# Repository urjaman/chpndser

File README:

CH340g-based debug serial dongle for the pandora ext port
----------------------------------------------------------

Parts list:
- usb mini b connector
- ch340g
- NX3008NBKW,115 SOT-323 n-ch mosfet
- 12Mhz HC-49 SMD crystal
- 2* 22pF 0603 cap
- 2* 0.1u 0603 cap
- 4* 4k7 0603 resistors
- pandora ext port connector

The PCB is shared at oshpark:
https://oshpark.com/shared_projects/jlOmwnKj
remember to pick the 0.8mm service

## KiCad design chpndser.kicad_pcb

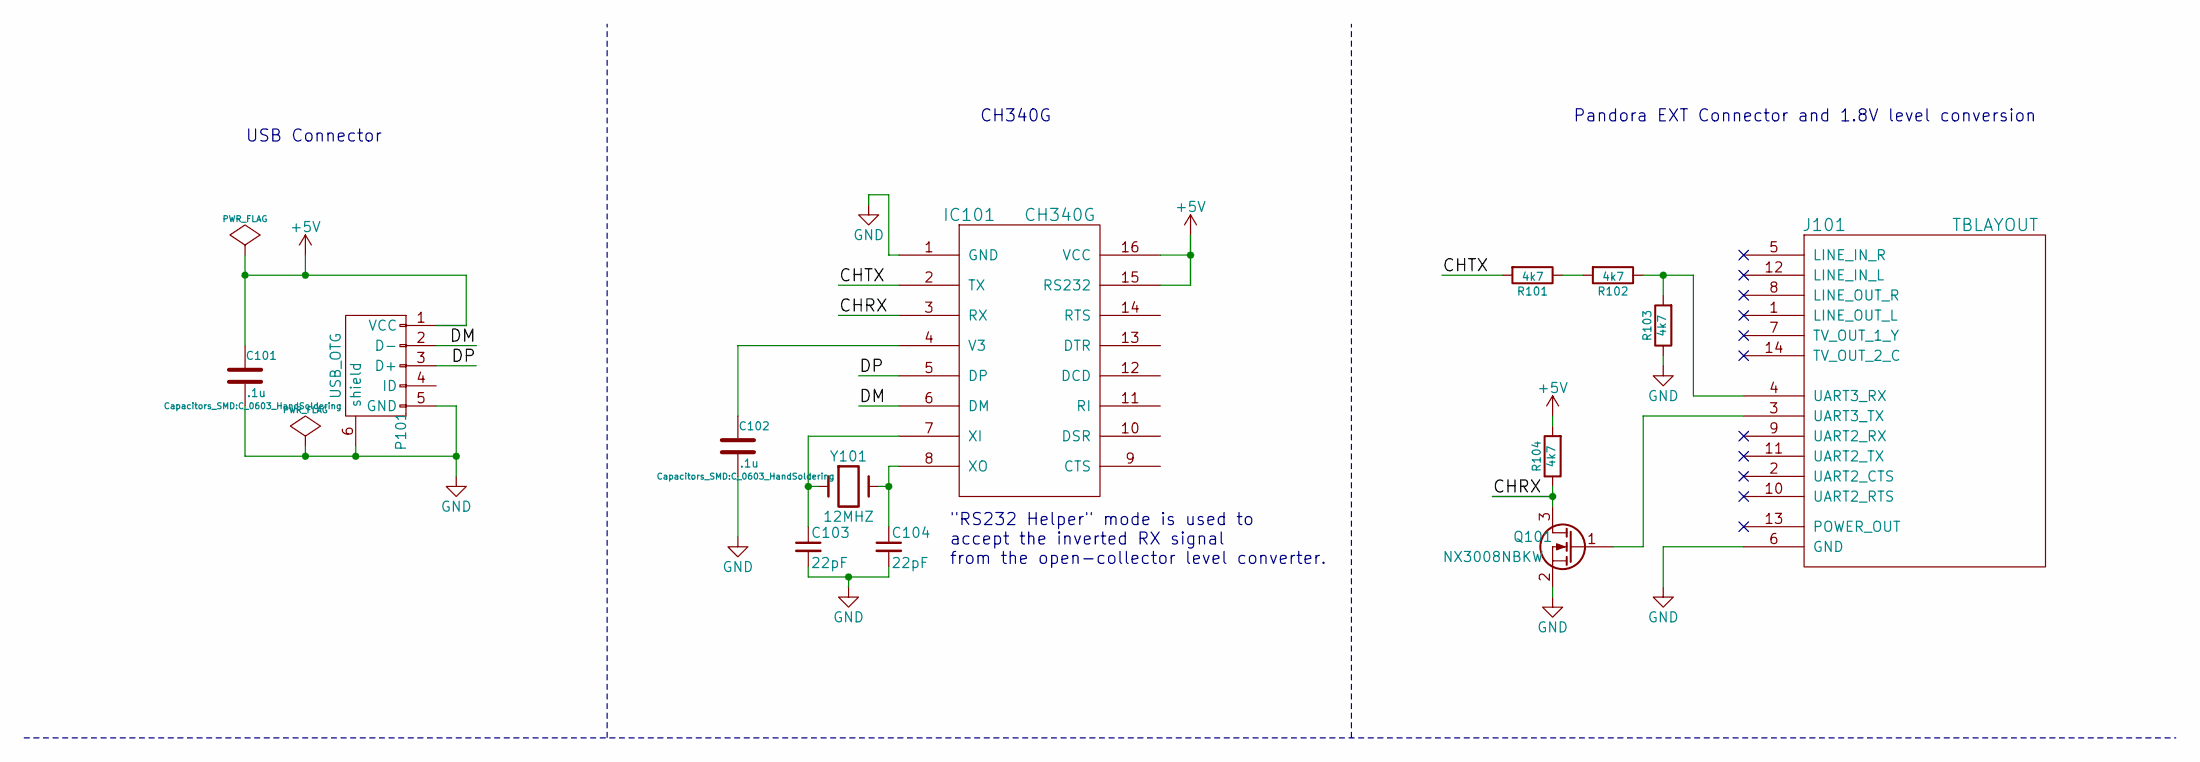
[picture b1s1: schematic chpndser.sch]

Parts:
C101, C102: .1u; C_0603_HandSoldering
C103, C104: 22pF; C_0603_HandSoldering
IC101: CH340G; SOIC-16_3.9x9.9mm_Pitch1.27mm
J101: TBLAYOUT; TBLAYOUT-ASTRON
P101: USB_OTG; USB_Mini-B
Q101: NX3008NBKW; SOT-323
R101, R102, R103, R104: 4k7; R_0603_HandSoldering
Y101: 12MHZ; Crystal_HC49-SD_SMD

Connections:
+5V: C101.1, IC101.15 (RS232), IC101.16 (VCC), P101.1 (VCC), R104.2
/CHRX: IC101.3 (RX), Q101.3 (D), R104.1
/CHTX: IC101.2 (TX), R101.2
/DM: IC101.6 (DM), P101.2 (D-)
/DP: IC101.5 (DP), P101.3 (D+)
GND: C101.2, C102.2, C103.2, C104.2, IC101.1 (GND), J101.6 (GND), P101.5 (GND), P101.6 (shield), Q101.2 (S), R103.1
unnamed: C102.1, IC101.4 (V3)
unnamed: C103.1, IC101.7 (XI), Y101.1
unnamed: C104.1, IC101.8 (XO), Y101.2
unnamed: J101.3 (UART3_TX), Q101.1 (G)
unnamed: J101.4 (UART3_RX), R102.1, R103.2
unnamed: R101.1, R102.2

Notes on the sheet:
USB Connector
CH340G
Pandora EXT Connector and 1.8V level conversion
"RS232 Helper" mode is used to accept the inverted RX signal from the open-collector level converter.

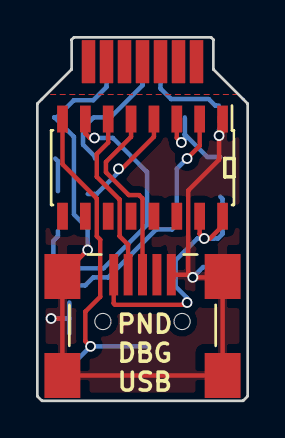
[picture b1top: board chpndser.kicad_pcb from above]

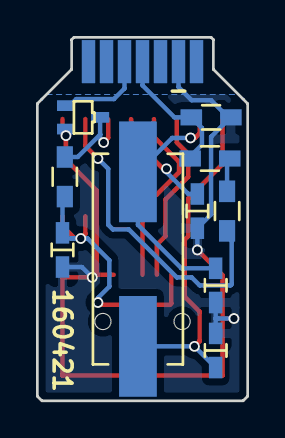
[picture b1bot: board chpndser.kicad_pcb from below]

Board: 2 copper layers, 11.7 x 20.2 mm, 13 parts (10 on the bottom side), 12 nets.

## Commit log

2016-03-15 First stuff
2016-03-16 better version
2016-12-15 First public release version
2016-12-15 add a note about the 0.8mm thing
